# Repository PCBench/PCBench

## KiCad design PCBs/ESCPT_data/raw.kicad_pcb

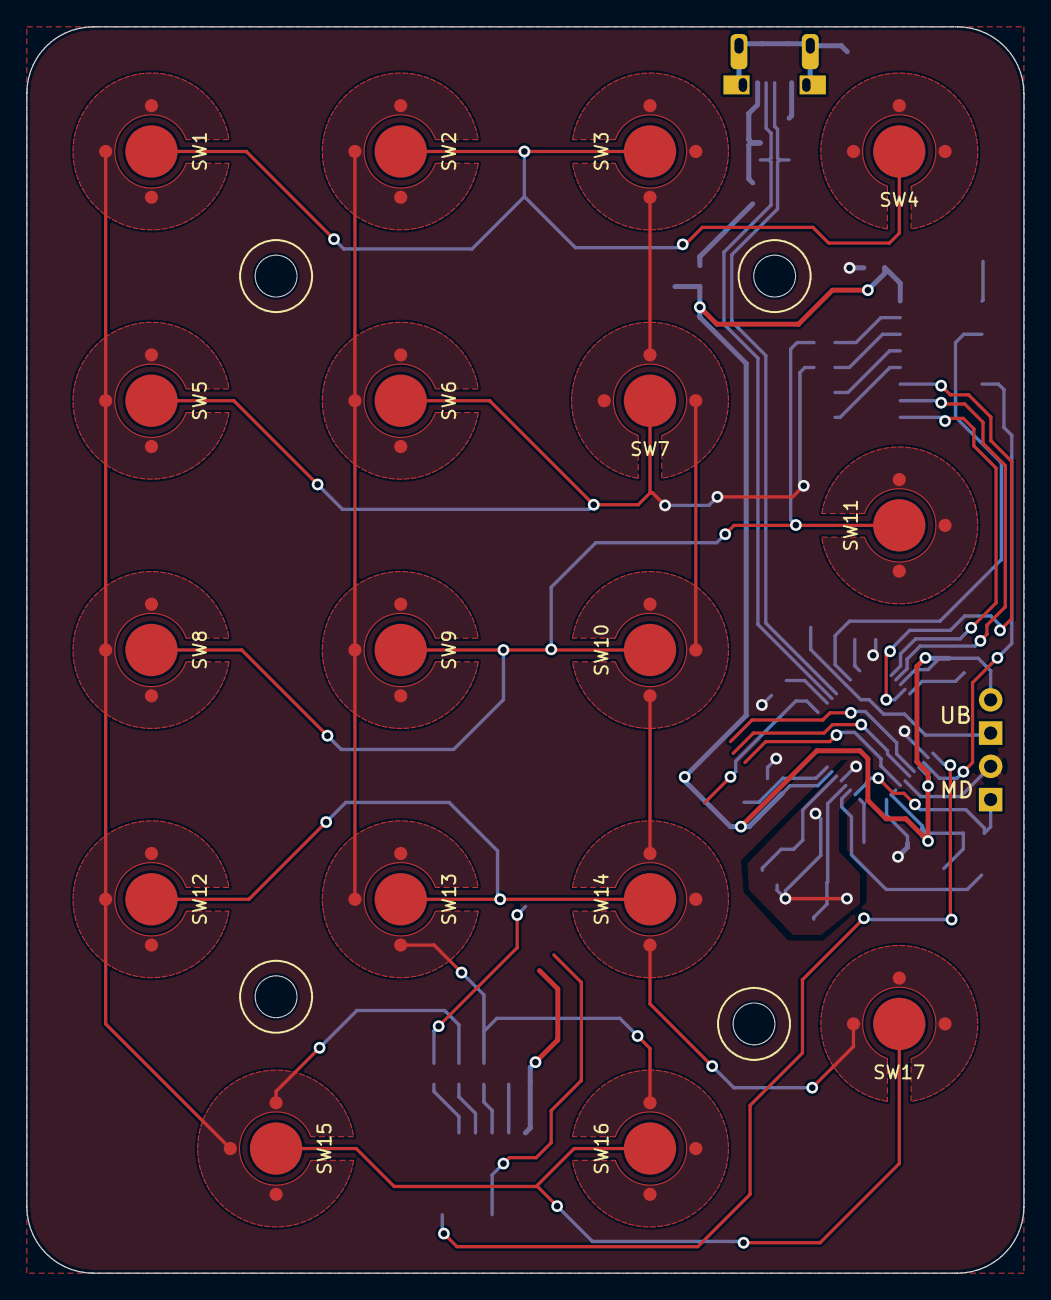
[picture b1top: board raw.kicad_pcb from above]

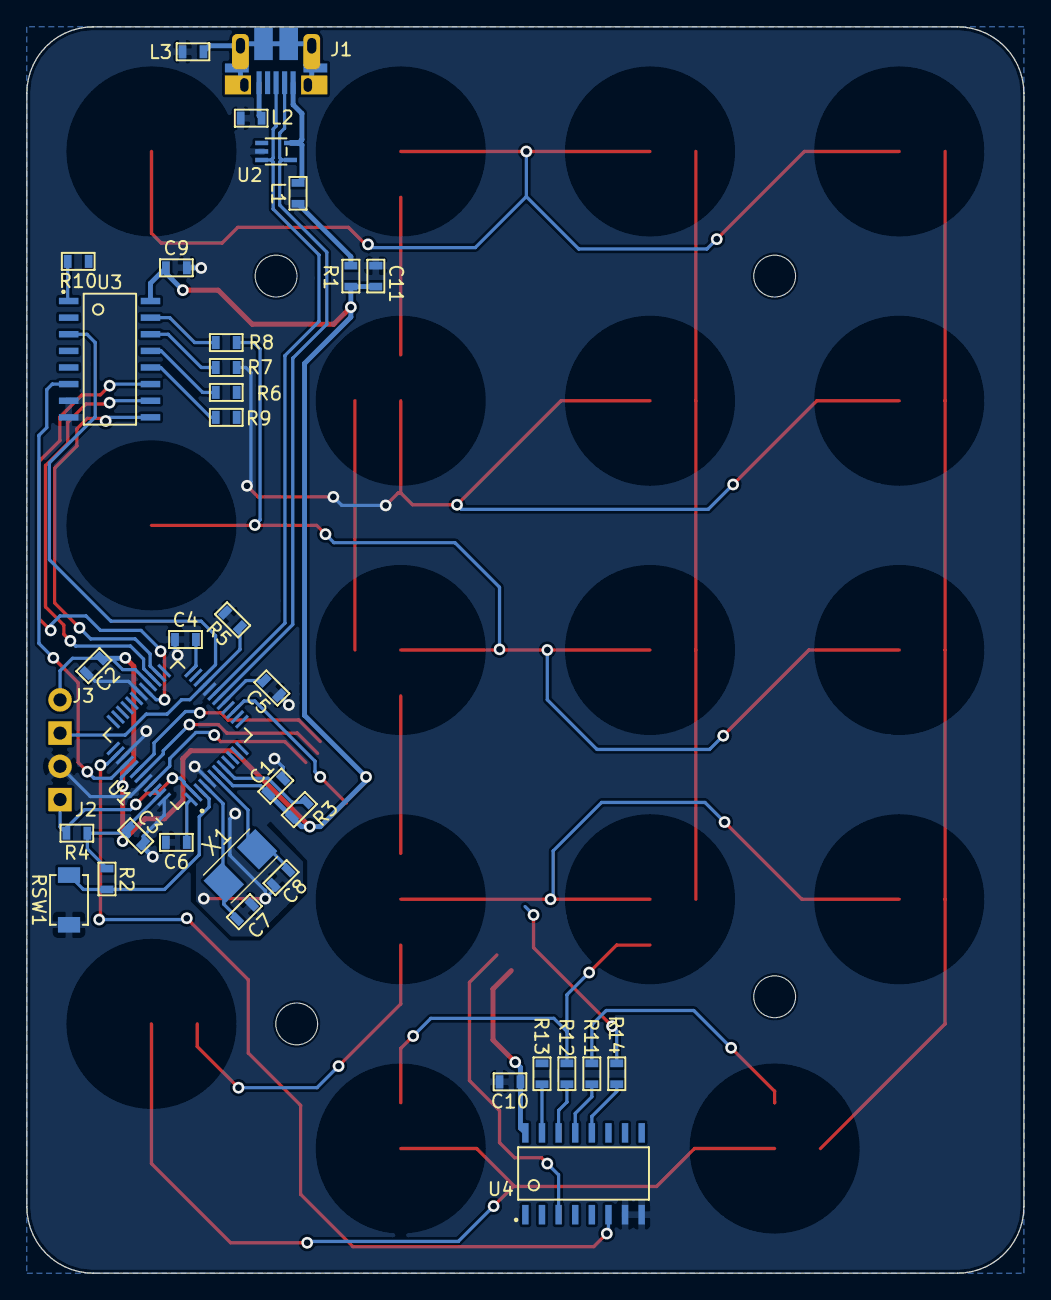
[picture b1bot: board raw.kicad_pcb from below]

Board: 2 copper layers, 76.2 x 95.2 mm, 58 parts (37 on the bottom side), 45 nets.

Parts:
C1, C2, C3, C9, C10: 100n; 0603_1608
C4: 10n; 0603_1608
C5: 330n; 0603_1608
C6, C11: 4u7; 0603_1608
C7, C8: 4p; 0603_1608
J1: MicroB; 10103594
J2, J3: CON2; J2
L1, L2, L3: INDUCTOR2; 0603_1608
R1: Polyswitch; 0603_1608
R2, R4: 4K7; 0603_1608_R
R3, R5: 10K; 0603_1608_R
R6, R7, R8, R9, R10, R11, R12, R13, R14: 470; 0603_1608_R
RSW1: SWITCH; TD_85XU
SR1, SR2, SR3, SR4: M3; M3NP
SW1, SW2, SW3, SW4, SW5, SW6, SW7, SW8, SW9, SW10, SW11, SW12, SW13, SW14, SW15, SW16, SW17: ESC_Pad_D
U1: R5F5231XAXFL; LQFP48-0.5
U2: DF5A6.8; SOT353
U3, U4: 74HC4051; SOIC16
X1: 12MHz; Crystal_5032

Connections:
/COL: U1.15, U4.3
/COL0: R11.1, SW1.2, SW5.2, SW8.2, SW12.2, SW15.2
/COL1: R12.1, SW2.2, SW6.2, SW9.2, SW13.2, SW16.2
/COL2: R13.1, SW3.2, SW7.2, SW10.2, SW14.2, SW17.2
/COL3: R14.1, SW4.2, SW11.2
/COL_A: U1.45, U4.11
/COL_B: U1.43, U4.10
/COL_C: U1.42, U4.9
/COL_INH: U1.38, U4.6
/MD: J2.1, R4.2, U1.2
/RESET: R2.2, RSW1.1, U1.3
/ROW: U1.22, U3.3
/ROW1: R6.1, SW1.1, SW2.1, SW3.1, SW4.1
/ROW2: R7.1, SW5.1, SW6.1, SW7.1
/ROW3: R8.1, SW8.1, SW9.1, SW10.1, SW11.1
/ROW4: R9.1, SW12.1, SW13.1, SW14.1
/ROW5: R10.1, SW15.1, SW16.1, SW17.1
/ROW_A: U1.29, U3.11
/ROW_B: U1.27, U3.10
/ROW_C: U1.26, U3.9
/ROW_INH: U1.40, U3.6
/TSCAP: C4.2, U1.24
/UB: J3.1, R5.1, U1.21
/USB_DM: J1.2, U1.18, U2.4
/USB_DP: J1.3, U1.19, U2.3
/VBUS: J1.1, L1.2, U2.5
GND: C1.2, C2.2, C3.2, C4.1, C5.1, C6.2, C7.2, C8.2, C9.2, C10.2, C11.2, J2.2, L2.1, L3.1, R5.2, RSW1.2, U1.5, U1.20, U1.30, U1.39, U1.44, U1.48, U2.2, U3.7, U3.8, U4.7, U4.8
unnamed: C5.2, U1.17
unnamed: C6.1, U1.1
unnamed: C7.1, U1.4, X1.2
unnamed: C8.1, U1.6, X1.1
unnamed: J1.5, L2.2
unnamed: J1.6, L3.2
unnamed: L1.1, R1.1
unnamed: R3.1, U1.8
unnamed: R6.2, U3.13
unnamed: R7.2, U3.14
unnamed: R8.2, U3.15
unnamed: R9.2, U3.12
unnamed: R10.2, U3.1
unnamed: R11.2, U4.13
unnamed: R12.2, U4.14
unnamed: R13.2, U4.15
unnamed: R14.2, U4.12
VCC: C1.1, C2.1, C3.1, C9.1, C10.1, C11.1, J3.2, R1.2, R2.1, R3.2, R4.1, U1.7, U1.28, U1.41, U1.46, U1.47, U3.16, U4.16

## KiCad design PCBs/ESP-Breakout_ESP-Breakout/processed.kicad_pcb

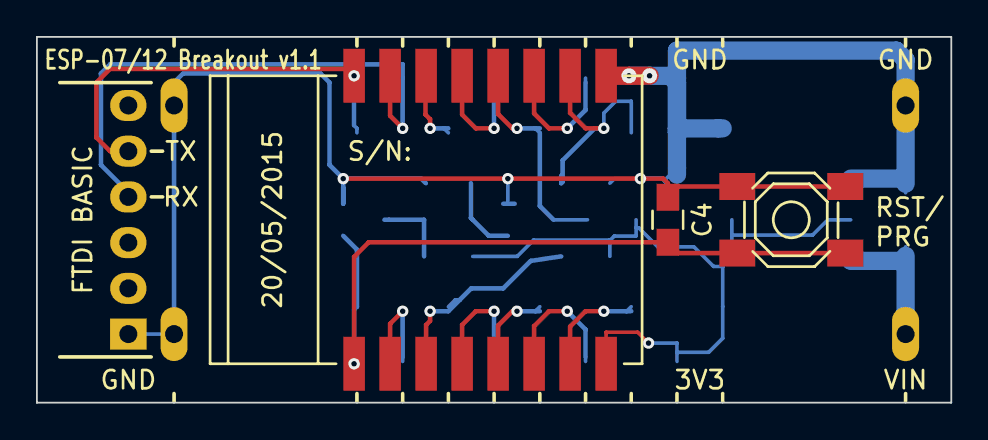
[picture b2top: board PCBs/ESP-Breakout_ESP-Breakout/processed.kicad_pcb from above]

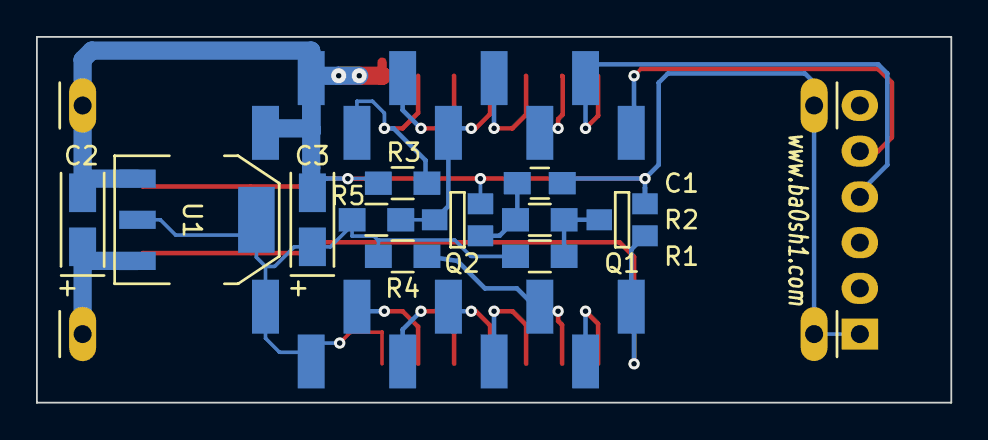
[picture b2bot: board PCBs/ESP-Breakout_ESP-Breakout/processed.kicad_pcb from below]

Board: 2 copper layers, 50.8 x 20.3 mm, 17 parts (13 on the bottom side), 19 nets.

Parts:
C1: 2u2; C_0805_HandSoldering
C2: 4u7; TantalC_SizeA_EIA-3216_Wave
C3: 22u; TantalC_SizeA_EIA-3216_Wave
C4: 0.1u; C_0805_HandSoldering
M1: ESP-07
P1: FTDI BASIC; Pin_Header_Angled_1x06
P2: CONN_01X11; SMD-PINHEADER-11A
P3: CONN_01X11; SMD-PINHEADER-11B
Q1, Q2: BSS138; SOT-23-GDS
R1: 470K; R_0805_HandSoldering
R2: 100K; R_0805_HandSoldering
R3, R5: 10K; R_0805_HandSoldering
R4: 47K; R_0805_HandSoldering
SW1: SW_PUSH; PUSH_4x4_SMD
U1: 1117-3.3; SOT-223

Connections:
+3V3: C3.1, M1.8, P3.9, P3.10, R1.1, R4.2, R5.2, U1.2
+5V: C2.1, P3.11, U1.3
/GPIO0: M1.12, P2.6, Q2.D, R5.1
/RESET: C4.1, M1.1, P3.2, Q1.G, SW1.2
/RXI: M1.16, P1.5, P2.2
/TXO: M1.15, P1.4, P2.3
GND: C1.2, C2.2, C3.2, C4.2, M1.9, P1.1, P2.1, P2.9, P2.10, P2.11, P3.1, Q1.S, Q2.S, R3.1, SW1.1, U1.1
unnamed: C1.1, Q2.G, R2.1
unnamed: M1.2, P3.3
unnamed: M1.3, P3.4, R4.1
unnamed: M1.4, P3.5
unnamed: M1.5, P3.6
unnamed: M1.6, P3.7
unnamed: M1.7, P3.8
unnamed: M1.10, P2.8, R3.2
unnamed: M1.11, P2.7
unnamed: M1.13, P2.5
unnamed: M1.14, P2.4
unnamed: Q1.D, R1.2, R2.2

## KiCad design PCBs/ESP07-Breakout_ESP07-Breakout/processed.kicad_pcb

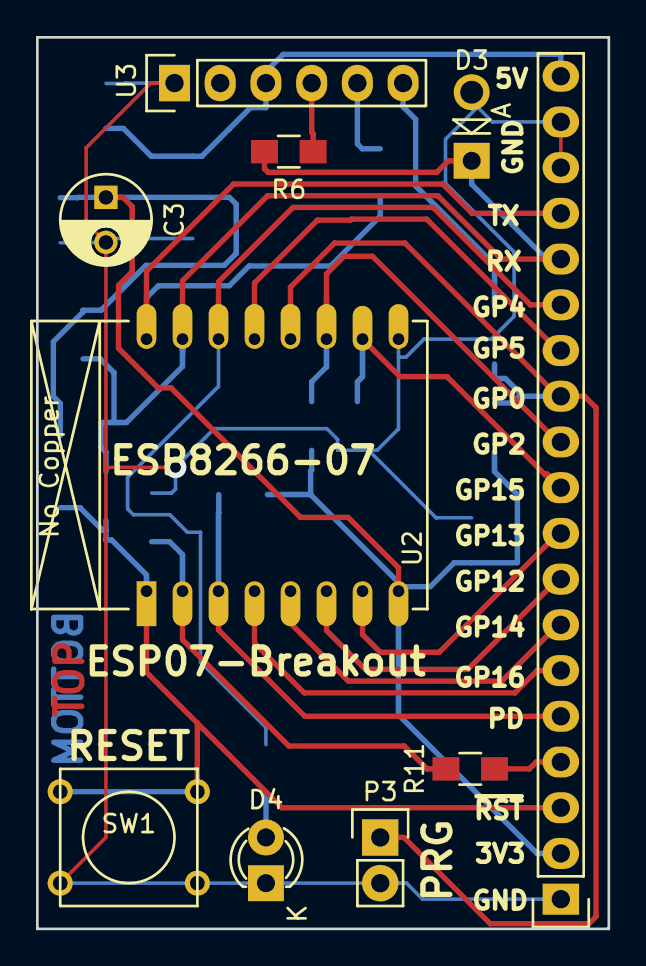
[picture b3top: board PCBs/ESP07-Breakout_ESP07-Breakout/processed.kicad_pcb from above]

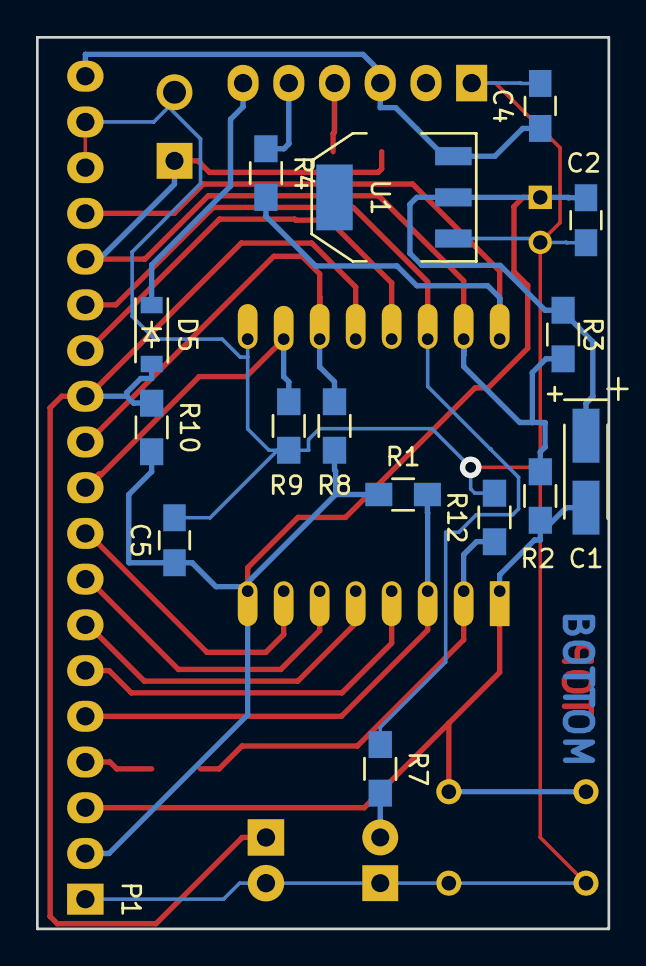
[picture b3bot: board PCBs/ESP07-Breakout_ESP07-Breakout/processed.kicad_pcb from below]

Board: 2 copper layers, 31.8 x 49.5 mm, 25 parts (15 on the bottom side), 22 nets.

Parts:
C1: 1u; TantalC_SizeA_EIA-3216_HandSoldering
C2, C4, C5: 100n; C_0805_HandSoldering
C3: 100u; C_Radial_D5_L6_P2.5
D3: 3V3; Diode_DO-41_SOD81_Vertical_AnodeUp
D4: LED; LED-3MM
D5: D; SOD-123
P1: Breakout; Pin_Header_Straight_1x19
P3: PRG; Pin_Header_Straight_1x02
R1, R3, R8, R9, R10, R11: 10k; R_0805_HandSoldering
R2: 41,2k; R_0805_HandSoldering
R4, R6, R7: 470; R_0805_HandSoldering
R12: 1k; R_0805_HandSoldering
SW1: RESET; SW_PUSH_SMALL
U1: AP1117D33; SOT-223
U2: ESP-07v2
U3: Serial-Header; Socket_Strip_Straight_1x06

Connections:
+3V3: C1.1, C2.1, C3.1, C5.1, P1.2, R1.1, R3.1, R8.1, R10.2, U1.2, U2.8
+5V: C4.1, P1.19, U1.3, U3.3
/ADC: R11.2, R12.1, U2.2
/AIN: P1.4, R11.1
/CH_PD: P1.5, R1.2, U2.3
/DTR: D5.1, U3.6
/GPIO0: D5.2, P1.12, P3.1, R10.1, U2.12
/GPIO2: P1.11, R8.2, U2.11
/GPIO5: P1.13, U2.13
/GPIO15: P1.10, R9.1, U2.10
/LED: P1.14, R7.1, U2.14
/RST: C1.2, P1.3, R2.2, SW1.1, U2.1
/RX: D3.1, P1.15, R2.1, R3.2, R6.2, U2.15
/RXF: R4.1, U3.5
/TX: P1.16, R4.2, U2.16
/TXF: R6.1, U3.4
GND: C2.2, C3.2, C4.2, C5.2, D3.2, D4.1, P1.1, P1.17, P1.18, P3.2, R9.2, R12.2, SW1.2, U1.1, U2.9, U3.1
unnamed: D4.2, R7.2
unnamed: P1.6, U2.4
unnamed: P1.7, U2.5
unnamed: P1.8, U2.6
unnamed: P1.9, U2.7

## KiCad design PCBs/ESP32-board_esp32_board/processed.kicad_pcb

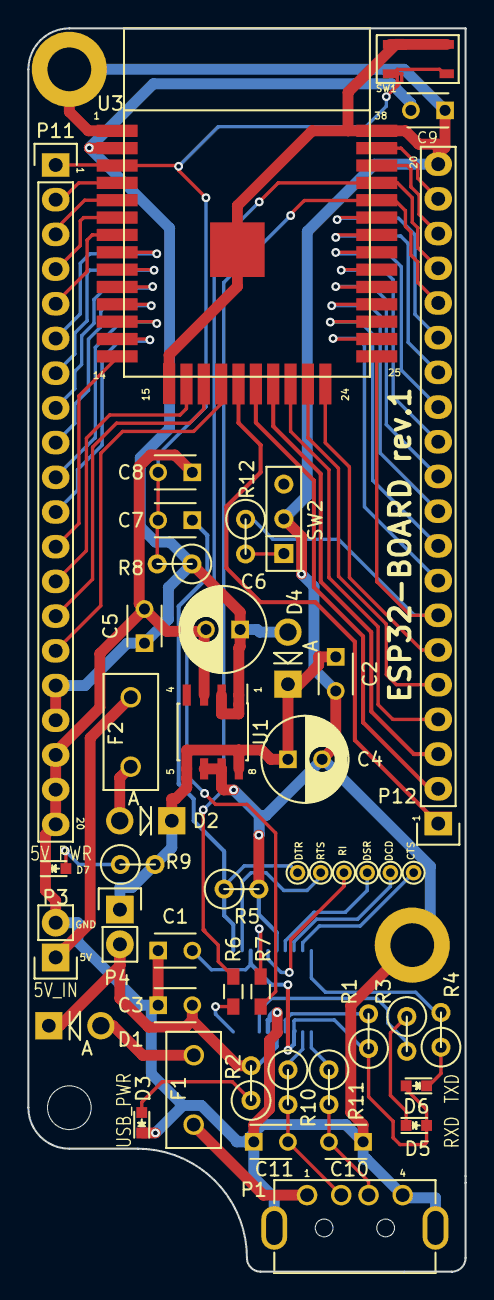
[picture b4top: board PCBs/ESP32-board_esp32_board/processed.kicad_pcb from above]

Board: 2 copper layers, 32.0 x 91.0 mm, 48 parts (1 on the bottom side), 63 nets.

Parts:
C1, C2, C3, C5, C7, C8, C9: 0.1u; C_Disc_D3_P2.5
C4, C6: 100u; C_Radial_D6.3_L11.2_P2.5
C10, C11: 47p; C_Disc_D3_P2.5
D1, D2: D; Diode_DO-41_SOD81_Vertical_AnodeUp
D3, D5, D6, D7: LED; LED_0603
D4: D_Schottky; Diode_DO-41_SOD81_Vertical_AnodeUp
F1, F2: FUSE; Fuse_TE5_Littlefuse-395Series
P1: USB_A
P3, P4: CONN_01X02; Pin_Header_Straight_1x02
P5, P6, P7, P8, P9, P10: CONN_01X01; PINTST
P11, P12: CONN_01X20; Pin_Header_Straight_1x20
R1, R8, R12: 10k; R1
R2, R3, R4, R5, R9: 1k; R1
R6, R7: 0; R_0603_HandSoldering
R10, R11: 27; R1
SW1: SW_PUSH; ALPS_SMD_SW
SW2: SPST; SW_Micro_SPST
U1: LT1963A_3.3V; SOIC-8_3.9x4.9mm_Pitch1.27mm
U2: FT231X; FT321X_SSOP
U3: ESP-WROOM-32

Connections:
+3.3VP: C1.2, D5.2, D6.2, R1.1, U2.3, U2.13
+3V3: C5.1, C6.1, C9.2, D4.2, P11.16, P11.17, R8.1, U1.1, U1.2, U3.2
+5V: C2.1, C4.1, D2.1, D4.1, P4.1, R9.2, U1.5, U1.8
+5VD: C3.2, D1.1, P4.2, R2.2, U2.15
CLK: P12.2, U3.20
CMD: P12.1, U3.19
CTS: P9.1, U2.9
DCD: P6.1, U2.8
DSR: P7.1, U2.7
DTR: C7.1, P8.1, R5.1, U2.1
EN: C7.2, C8.2, P11.1, R8.2, SW1.2, U3.3
ESP_RXD: P12.16, R6.1, U3.34
ESP_TXD: P12.17, R7.1, U3.35
GND: C1.1, C2.2, C3.1, C4.2, C5.2, C6.2, C8.1, C9.1, C10.1, C11.1, D3.1, D7.1, P1.4, P1.5, P3.2, P11.18, P11.19, P11.20, P12.20, R5.2, SW1.1, SW2.2, U1.3, U1.6, U1.7, U2.6, U2.16, U3.1, U3.15, U3.38
IO0: P12.7, R12.1, U3.25
IO2: P12.6, U3.24
IO4: P12.8, U3.26
IO5: P12.11, U3.29
IO12: P11.12, U3.14
IO13: P11.13, U3.16
IO14: P11.11, U3.13
IO15: P12.5, U3.23
IO16: P12.9, U3.27
IO17: P12.10, U3.28
IO18: P12.12, U3.30
IO19: P12.13, U3.31
IO21: P12.15, U3.33
IO22: P12.18, U3.36
IO23: P12.19, U3.37
IO25: P11.8, U3.10
IO26: P11.9, U3.11
IO27: P11.10, U3.12
IO32: P11.6, U3.8
IO33: P11.7, U3.9
IO34: P11.4, U3.6
IO35: P11.5, U3.7
NC: P12.14, U3.32
unnamed: C10.2, P1.3, R11.2
unnamed: C11.2, P1.2, R10.2
unnamed: D1.2, F1.2
unnamed: D2.2, F2.2
unnamed: D3.2, R2.1
unnamed: D5.1, R3.1
unnamed: D6.1, R4.1
unnamed: D7.2, R9.1
unnamed: F1.1, P1.1
unnamed: F2.1, P3.1
unnamed: R1.2, U2.14
unnamed: R3.2, U2.17
unnamed: R4.2, U2.10
unnamed: R6.2, U2.20
unnamed: R7.2, U2.4
unnamed: R10.1, U2.12
unnamed: R11.1, U2.11
unnamed: R12.2, SW2.1
RI: P5.1, U2.5
RTS: P10.1, U2.2
SD0: P12.3, U3.21
SD1: P12.4, U3.22
SD2: P11.14, U3.17
SD3: P11.15, U3.18
SENSOR_VN: P11.3, U3.5
SENSOR_VP: P11.2, U3.4

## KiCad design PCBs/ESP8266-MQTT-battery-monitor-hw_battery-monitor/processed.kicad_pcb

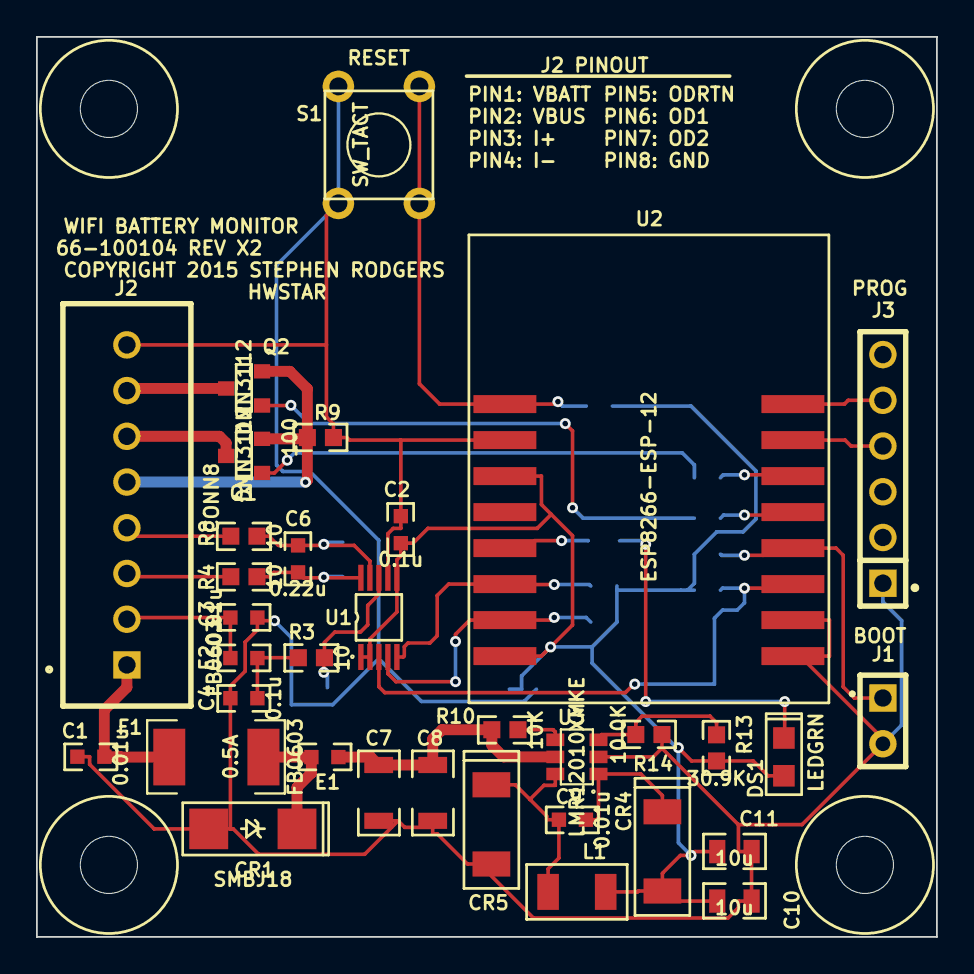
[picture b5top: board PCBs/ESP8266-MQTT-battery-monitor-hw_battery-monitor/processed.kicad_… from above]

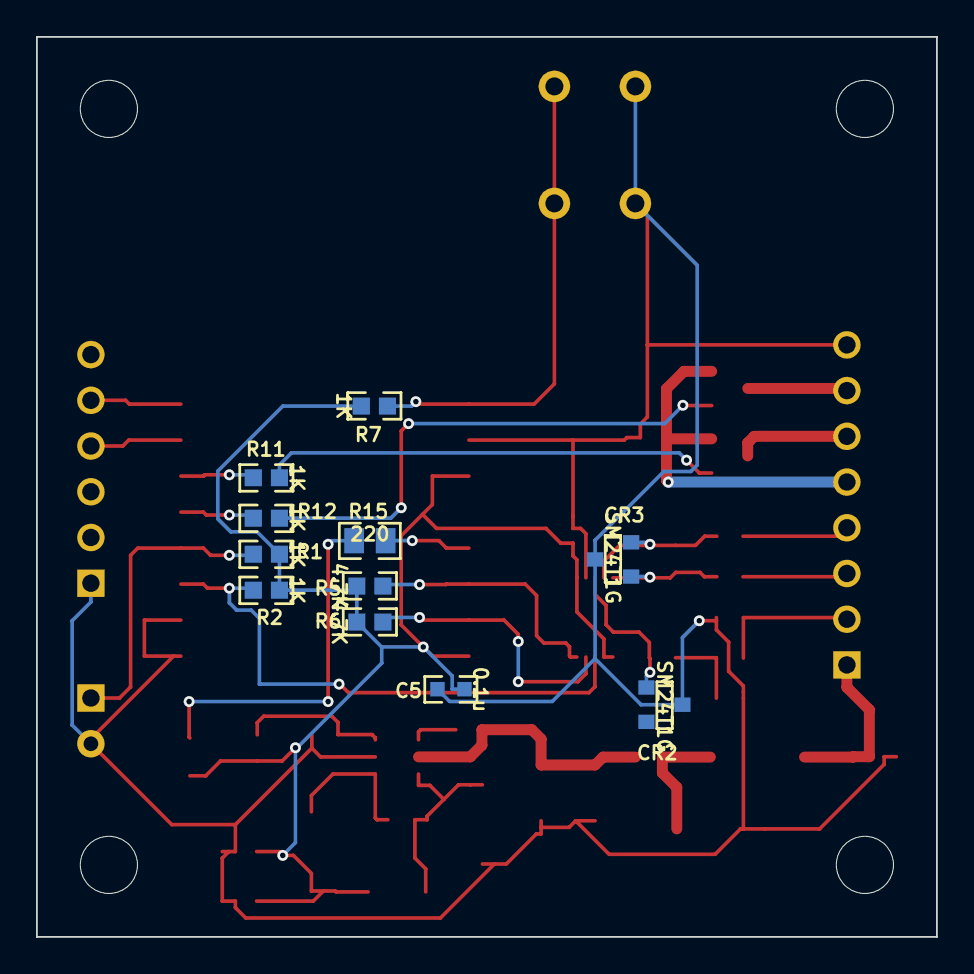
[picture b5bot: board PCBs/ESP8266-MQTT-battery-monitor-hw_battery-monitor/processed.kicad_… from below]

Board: 2 copper layers, 50.0 x 50.0 mm, 49 parts (11 on the bottom side), 32 nets.

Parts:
C1, C3, C9: 0.01u; CC0603
C2, C4, C5: 0.1u; CC0603
C6: 0.22u; CC0603
C7, C8: 10u; CC1206
C10, C11: 10u; CC0805
CR1: SMBJ18; SMB-SAR
CR2, CR3: SM24T1G; SOT23-3-SAR
CR4, CR5: CMS06; M-FLAT-SAR
DS1: LEDGRN; LED0805
E1, E2: FB0603; CC0603
F1: 0.5A; MINISMD1812
J1: CONN2; BERG2
J2: CONN8; PHOENIX254-8
J3: CONN6; BERG6
L1: 10uH; IND1210
MTG-HOLE-125-RING-300, MTG-HOLE-125-RING-300_2, MTG-HOLE-125-RING-300_3, MTG-HOLE-125-RING-300_4: VAL**; MTG-HOLE-125-RING-300
Q1, Q2: DMN3112; SOT23-3-SAR
R1, R2, R7, R11, R12: 1K; RC0603
R3, R4, R8: 10; RC0603
R5, R6: 4.7K; RC0603
R9: 100; RC0603
R10: 10K; RC0603
R13: 30.9K; RC0603
R14: 10.0K; RC0603
R15: 220; RC0805
S1: SW_TACT; SW_TACT_6MM
U1: INA226; MSOP-10-SAR
U2: ESP8266-ESP-12; ESP8266-ESP12
U3: LMR12010XMKE; SOT23-6-SAR

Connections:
+3.3V: C2.1, C5.1, C10.1, C11.1, CR4.1, DS1.1, L1.2, R1.1, R2.1, R5.1, R6.1, R7.1, R13.1, U1.1, U1.2, U1.6, U2.3, U2.8
/ALERT: R2.2, U1.3, U2.11
/CONNLED: R15.1, U2.5
/OD1: J2.6, Q1.3
/OD2: J2.7, Q2.3
/ODRTN: J2.5, Q1.2, Q2.2, R9.1
/OUT1: R11.2, U2.14
/OUT2: R12.2, U2.13
/RXD: J3.4, U2.15
/SCL: R5.2, U1.5, U2.6
/SDA: R6.2, U1.4, U2.7
/TXD: J3.5, U2.16
/VBIN: C1.1, F1.1, J2.1
/VBINF: CR1.2, E1.1, F1.2
/VBOOST: C9.1, CR4.2, U3.1
/VBUS: CR2.1, R3.1, U1.8
/VFB: R13.2, R14.1, U3.3
/VIN+: C6.1, CR3.1, R4.1, U1.10
/VIN-: C6.2, CR3.2, R8.1, U1.9
/VSW: C9.2, CR5.2, L1.1, U3.6
GND: C1.2, C2.2, C3.2, C4.2, C5.2, C7.2, C8.2, C10.2, C11.2, CR1.1, CR2.3, CR3.3, CR5.1, J1.2, J2.8, J3.1, R9.2, R14.2, S1.1, S1.2, U1.7, U2.2, U2.9, U2.10, U3.2
unnamed: C3.1, E2.1, J2.2
unnamed: C4.1, E2.2, R3.2
unnamed: DS1.2, R15.2
unnamed: J1.1, R1.2, U2.12
unnamed: J2.3, R4.2
unnamed: J2.4, R8.2
unnamed: Q1.1, R11.1
unnamed: Q2.1, R12.1
unnamed: R7.2, S1.3, S1.4, U2.1
unnamed: R10.1, U3.4
VBATT: C7.1, C8.1, E1.2, R10.2, U3.5

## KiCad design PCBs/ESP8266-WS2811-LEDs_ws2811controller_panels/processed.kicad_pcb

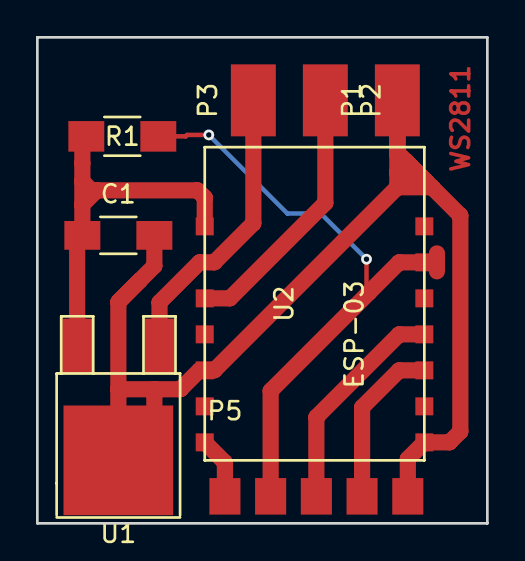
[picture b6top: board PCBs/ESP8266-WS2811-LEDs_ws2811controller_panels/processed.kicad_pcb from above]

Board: 2 copper layers, 25.0 x 27.0 mm, 8 parts (0 on the bottom side), 8 nets.

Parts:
C1: 22u; C_1206_HandSoldering
P1: PSU_GND; SolderPad
P2: PSU_EN; SolderPad
P3: PSU_5V; SolderPad
P5: DEBUG_HDR; 5pin_SMD
R1: 10K; R_1206_HandSoldering
U1: LF33; TO-252-2Lead
U2: ESP-03; esp-03

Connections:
+3V3: C1.1, R1.2, U1.3, U2.8
+5V: P3.1, U1.1
/CH_PD: P5.2, R1.1, U2.6
/FLASH_EN: P5.1, U2.14
/PSU_EN: P2.1, U2.10
/UART_RX: P5.3, U2.4
/UART_TX: P5.4, U2.3
GND: C1.2, P1.1, P5.5, U1.2, U2.1, U2.12

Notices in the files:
PCBs/ESP8266-MQTT-battery-monitor-hw_battery-monitor/processed.kicad_pcb:
COPYRIGHT 2015 STEPHEN RODGERS
